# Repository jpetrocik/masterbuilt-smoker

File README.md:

# Smart Smoker Controller System

This project replaces the standard control board in an electric smoker, adding Wi-Fi, PID heat control, four built-in meat probes, a companion mobile app, and more. I can remotely monitor and control the cook from anywhere without being tied down to the smoker. The custom PID algorithm maintains an almost perfect internal temperature with minimal fluctuations. A variety of push notifications eliminate the need to constantly check on the cook throughout the day and night.

The primary goal of this project is to give me my weekend back. I don't want to constantly babysit the smoker when I rather be spending the day snowboarding, hitting trails, off-roading, or just hanging out with friends. The controller continuously monitors the smoker and meat temperature, sending real-time notifications to my phone when probes hit their target temperatures.

This specific board was designed as a drop-in replacement for Masterbuilt refrigerator-style smokers, but the system can be adapted to work with almost any electric smoker.

## Overview

This repository is split into four major components, each with its own detailed `README.md` file:

### 1. Mobile App (./www/README.md)
A Progressive Web App (PWA) that can be installed on your phone to run exactly like a native app, complete with real-time push notifications.

### 2. Backend (./server/README.md)
The central nervous system of the project. It acts as the bridge between the physical smoker and the mobile application. The backend handles the complex algorithms for stall detection and logs high-resolution temperature history. The system is highly fault-tolerant: if the backend drops offline, the firmware will continue executing the active cook locally. If the backend loses connection to the smoker, an alert is sent immediately to your phone.

### 3. Firmware (./firmware/README.md)
The embedded code running on the physical microcontroller (ESP32) that directly interfaces with the smoker's hardware.

### 4. Hardware & PCBs (./hardware/README.md)
This directory contains the custom board designs. Currently, there are two boards designed to support Masterbuilt smokers: the main controller PCB and the power module. The custom power module replaces the stock mechanical relay with a Solid State Relay (SSR) to easily tolerate the rapid on/off switching required by the PID heat control.

## 📂 Repository Structure

```text
├── /server             # Node.js backend
├── /firmware           # Microcontroller code (ESP32/Arduino)
├── /www                # React / Vite / Tailwind PWA
├── /hardware           # Schematics and Gerber files
└── README.md           # Project overview (You are here)

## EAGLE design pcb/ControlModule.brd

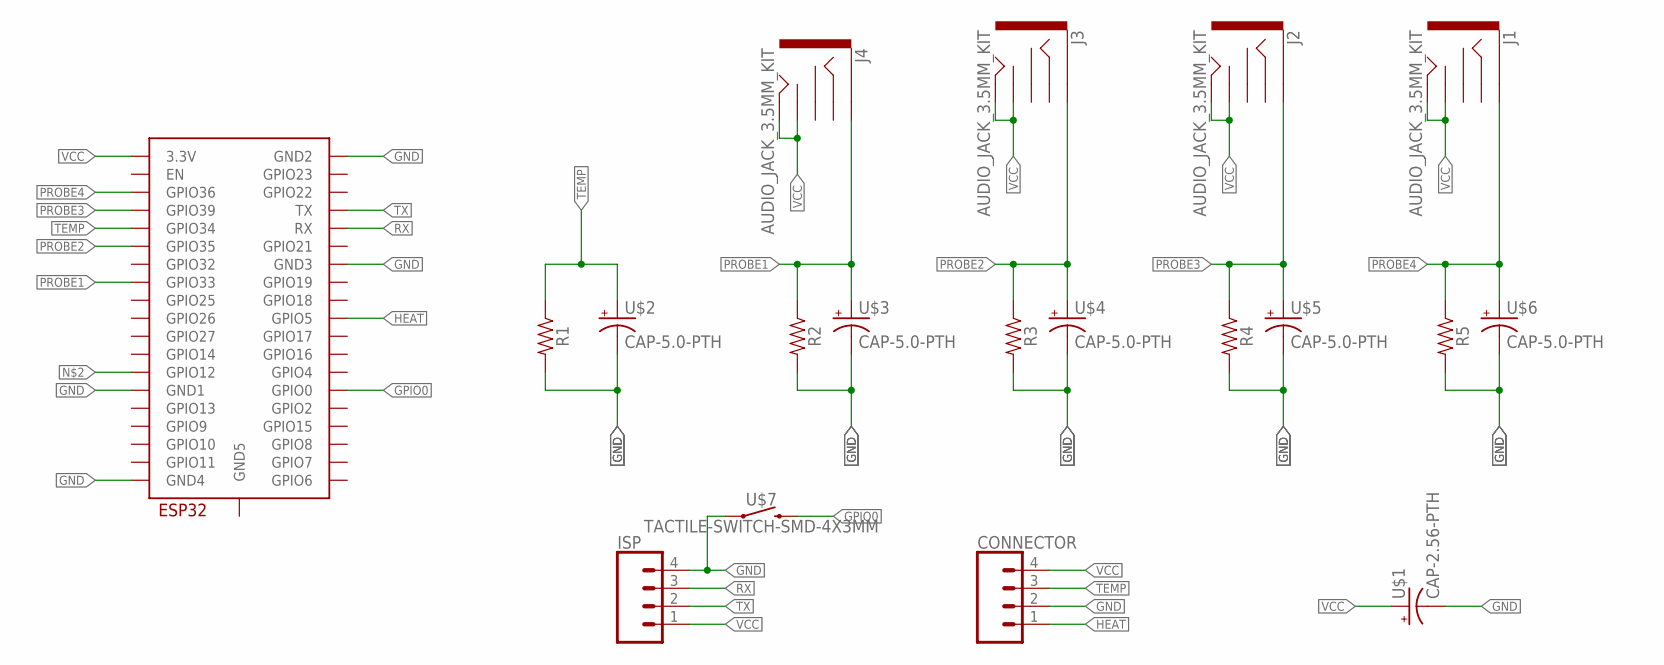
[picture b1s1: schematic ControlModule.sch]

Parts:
CONNECTOR: CONN_04PTH; 1X04
ISP: CONN_04PTH; 1X04
J1, J2, J3, J4: AUDIO_JACK_3.5MM_KIT; AUDIO-JACK-KIT
R1, R2, R3, R4, R5: 0805
U$1: CAP-2.56-PTH; CAP-PTH-2.5MM-5MM
U$2, U$3, U$4, U$5, U$6: CAP-5.0-PTH; CAP-PTH-5MM
U$7: TACTILE-SWITCH-SMD-4X3MM; TACTILE_SWITCH_SMD_4X3MM
U$8: ESP32-WROOM

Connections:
GND: CONNECTOR.2, ISP.4, R1.2, R2.2, R3.2, R4.2, R5.2, U$1.2 (-), U$2.2 (-), U$3.2 (-), U$4.2 (-), U$5.2 (-), U$6.2 (-), U$7.1, U$8.GND1, U$8.GND2, U$8.GND3, U$8.GND4
GPIO0: U$7.2, U$8.IO0 (GPIO0)
HEAT: CONNECTOR.1, U$8.IO5 (GPIO5)
PROBE1: J4.SLEEVE, R2.1, U$3.1 (+), U$8.IO33 (GPIO33)
PROBE2: J3.SLEEVE, R3.1, U$4.1 (+), U$8.IO35 (GPIO35)
PROBE3: J2.SLEEVE, R4.1, U$5.1 (+), U$8.SENSOR_VN (GPIO39)
PROBE4: J1.SLEEVE, R5.1, U$6.1 (+), U$8.SENSOR_VP (GPIO36)
RX: ISP.3, U$8.RX
TEMP: CONNECTOR.3, R1.1, U$2.1 (+), U$8.IO34 (GPIO34)
TX: ISP.2, U$8.TX
VCC: CONNECTOR.4, ISP.1, J1.TIP, J1.TSH, J2.TIP, J2.TSH, J3.TIP, J3.TSH, J4.TIP, J4.TSH, U$1.1 (+), U$8.3V3 (3.3V)

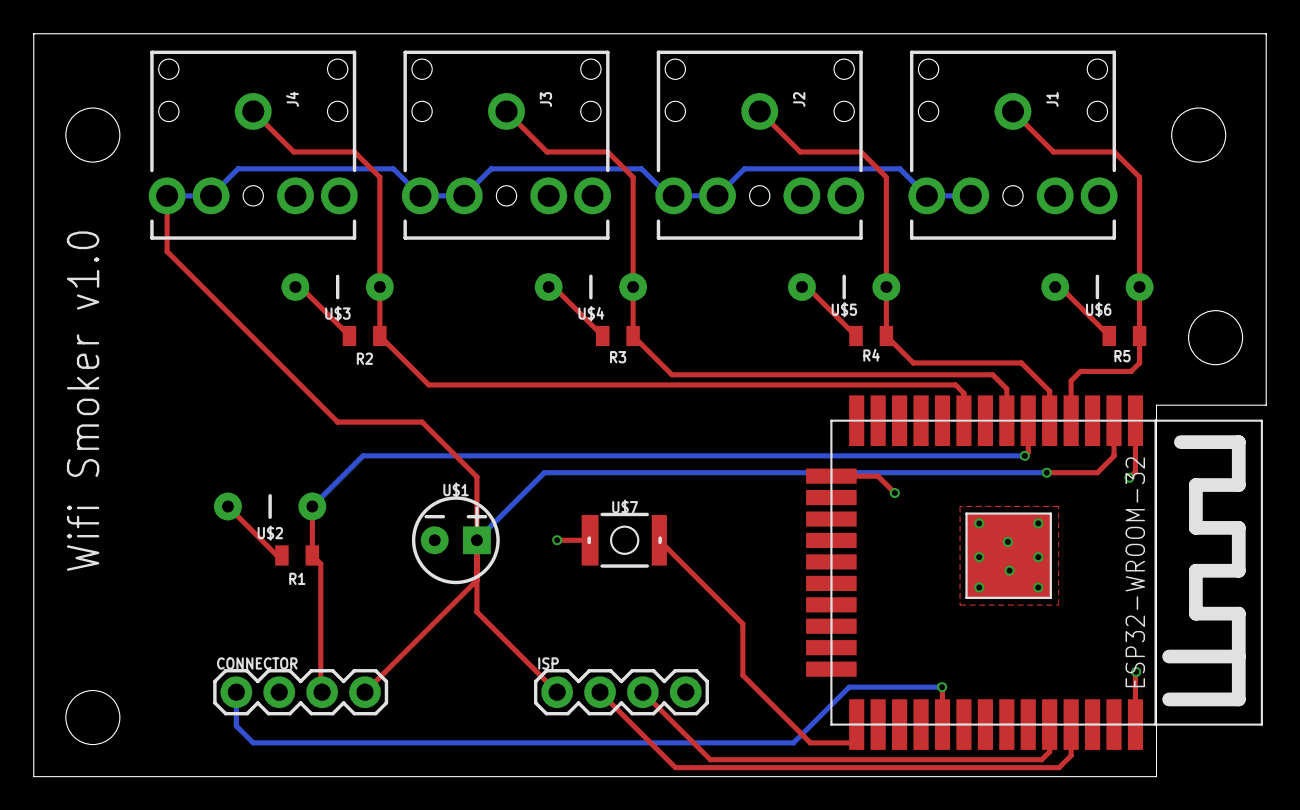
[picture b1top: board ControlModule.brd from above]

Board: 2 copper layers, 73.0 x 44.0 mm, 19 parts (0 on the bottom side), 11 nets.

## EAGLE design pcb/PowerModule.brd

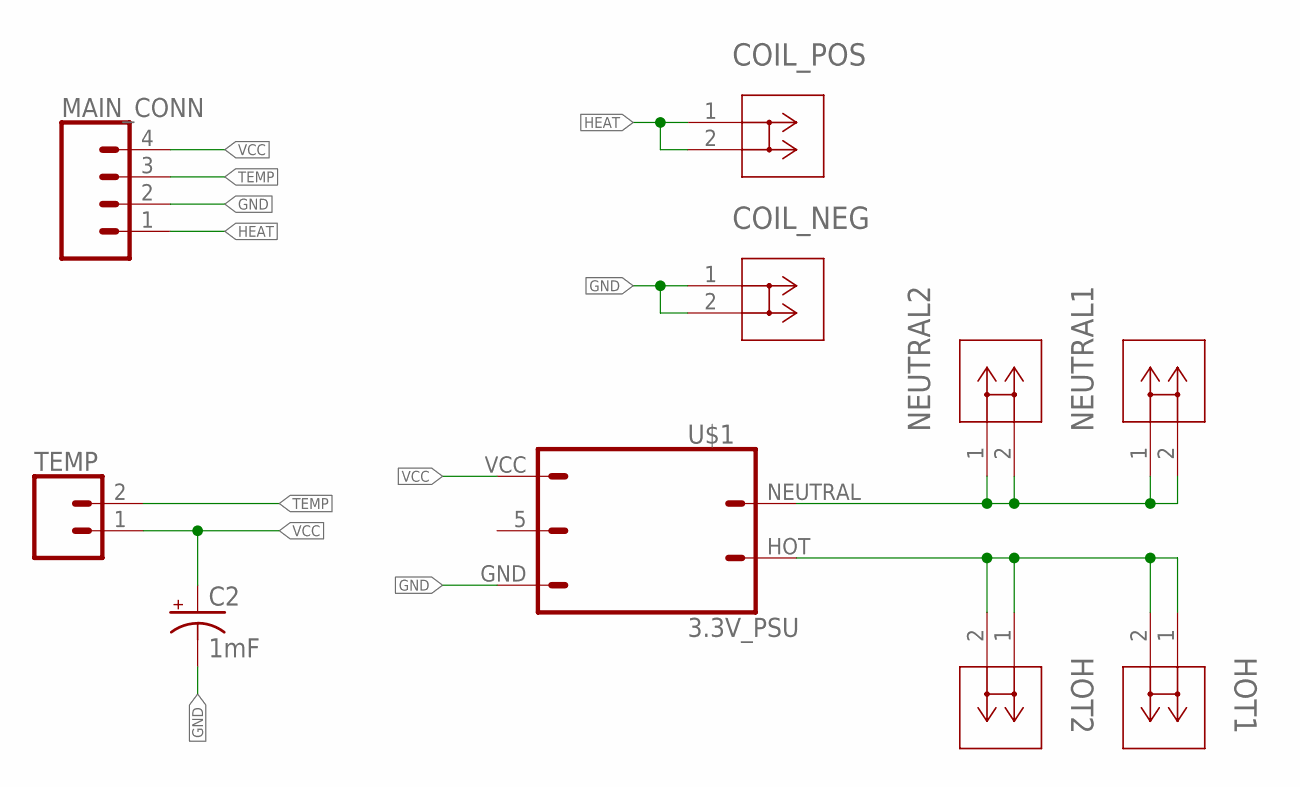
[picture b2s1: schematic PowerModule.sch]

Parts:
C2: 1mF; CPOL-RADIAL-5MM-10MM
COIL_NEG: 1287; CONN_1287_KEY
COIL_POS: 1287; CONN_1287_KEY
HOT1, HOT2: 1287; CONN_1287_KEY
MAIN_CONN: CONN_04PTH; 1X04
NEUTRAL1, NEUTRAL2: 1287; CONN_1287_KEY
TEMP: CONN_02; 1X02
U$1: 3.3V_PSU; 1X03

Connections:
GND: C2.-, COIL_NEG.1, COIL_NEG.2, MAIN_CONN.2, U$1.GND
HEAT: COIL_POS.1, COIL_POS.2, MAIN_CONN.1
HOT: HOT1.1, HOT1.2, HOT2.1, HOT2.2, U$1.HOT
NEUTRAL: NEUTRAL1.1, NEUTRAL1.2, NEUTRAL2.1, NEUTRAL2.2, U$1.NEUTRAL
TEMP: MAIN_CONN.3, TEMP.2
VCC: C2.+, MAIN_CONN.4, TEMP.1, U$1.VCC

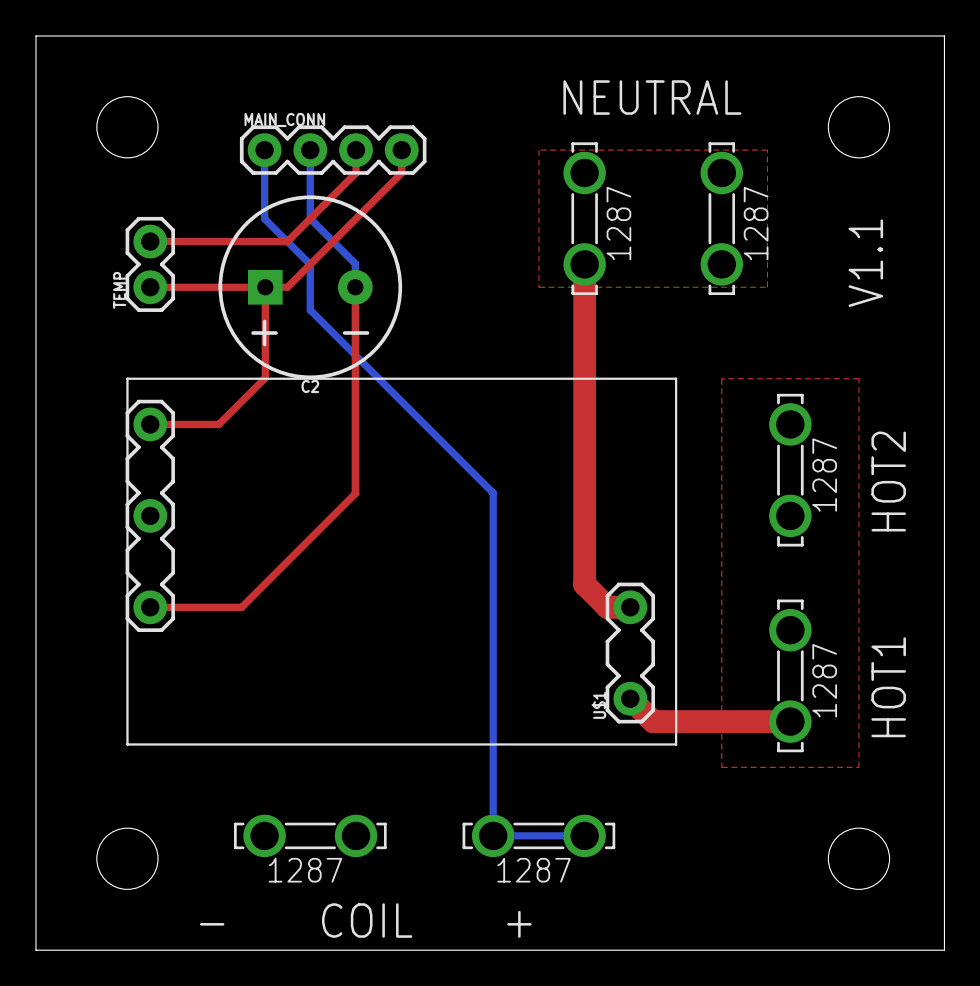
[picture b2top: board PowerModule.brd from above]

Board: 2 copper layers, 50.5 x 50.8 mm, 10 parts (0 on the bottom side), 6 nets.

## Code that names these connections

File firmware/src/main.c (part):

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#define MEAT_PROBE3                  ADC_CHANNEL_3
#define MEAT_PROBE4                  ADC_CHANNEL_4

#define HEAT_PIN 5

#define ADC_SAMPLE_SIZE 8

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cJSON *json = cJSON_Parse("{\"title\":\"Hello World\"}");

    double temperature = 0;
    double probe1 = 0;
    double probe2 = 0;
    double probe3 = 0;
    double probe4 = 0;
    long lastRead = 0;
    long now;
    bool abortError = false;
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
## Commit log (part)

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2022-12-12 Inital commit
2022-12-12 WebSocket
2022-12-12 probes
2022-12-13 No working PID
2022-12-14 Working PID
2022-12-17 Added cookEndTime
2023-01-18 Added probe
2023-02-26 New PROBE_A/B/C
2023-02-27 Added OTA
2023-02-27 Tweaker kp,ki,kd
2023-03-09 Tweaking temp coiffients
2023-03-09 Added eagle files
2023-03-09 Create README.md
    Added readme.md
2023-03-12 using adc functions and new thermistor a/b/c
2023-08-22 Initial commit after some calibration
2023-08-24 Port of PIP
2025-03-12 Add kicad files
2025-05-29 kicad files
2025-05-29 compiles
2025-06-02 Switching to ADS1115
2025-06-03 Probes working with ADS1115
2025-08-02 board version 2.0
2025-08-02 Renamed files
2025-08-12 Removed escape character
2025-08-12 Added developement notes
2025-08-12 Added deep orange theme samples
2025-08-13 Removed bad files
2025-08-13 Added LCD support
2025-08-13 Added define to enable/disable LCD
2025-08-13 upstream lv.conf
2025-08-13 Configure lv.conf file
2025-08-15 Added initial mqqtt support (WIP)
2025-08-15 Configure TFT User_Setup.h
2025-08-15 Moved websoceket and wfi code into sperate files
2025-08-15 Cleaned up UI and better wifi init
2025-08-15 mqtt publish status working
2025-08-15 Changed CommandEvent handling to parse in main.cpp
2025-08-25 Fixed devide by zero error
2025-08-25 Fix overflow issue
2025-08-25 Updated probe ABC numbers
2025-08-26 Temp ABC
2025-08-26 New ABC
2025-08-26 add set check limits
2025-08-26 Cleaned up logging
2025-08-26 Added last will MQTT message
2025-08-27 Added debugProbe and new ABC values
2025-08-27 Added back dutyCycle
2025-08-27 new temp abc
2025-08-27 Cleanup debug code
2025-09-08 Improved PID and ABC settings
2025-09-08 Minor layout improvements
2025-10-06 v2.1 controller
2025-10-06 Added power modules board
2025-10-07 Adding assests
2025-10-07 update board with lcd
2025-10-11 Fixed issue with UI not compiling
2025-10-13 Removed delay in lcd_loop
2026-01-19 Controller v2.1.1
2026-03-11 Added server backend code
2026-03-11 Added missing spec
2026-03-11 SPEC 0.1 complete
2026-03-11 Initial SPEC 0.2
2026-03-11 initial frontend pass
2026-03-11 Updated state information
2026-03-11 Added Elaspe Time
2026-03-12 Added presence LWT and removed device topic code
2026-03-12 Added simulator
2026-03-12 Renames json properties from probe[X][Property] and prefixed smoker
2026-03-12 Fixed boolean issue with sqllite
2026-03-12 Add similutor launch and .gitignore for sqllite data files
2026-03-12 First pass connected to backend
2026-03-12 Fixed infinite loop and localstorage usage
2026-03-12 Fixed display issue with historical data
2026-03-13 Fixed histroical data
2026-03-14 Firebase
2026-03-18 Firebase notification
2026-03-19 SetTemperature
2026-03-19 SetCookTimer
2026-03-19 sendCommand
2026-03-19 WebSocket nanny
2026-03-19 SmokerId picker
2026-03-19 Deployable build
2026-03-19 Make live data renderig faster
2026-03-19 Presences
2026-03-19 functional complete
2026-03-21 Added simulator command line arguments
2026-03-21 Fixed issue with parsing command line arguments
2026-03-21 Fixed mixed up between probeTemp and probeTarget
2026-03-21 Added manifest
2026-03-23 Create icon assests and icons
2026-03-24 Improved temperature simulation
2026-03-24 Added stale notification and cleaned up notification code
2026-03-24 Improve the telemetry data requirement based on calculated telemetry intervals
2026-03-24 Speed up probe telemetry growth
2026-03-24 Fixed issue with alert on new smoker
2026-03-24 Default notification to true so on startup they are not fired
2026-03-24 Fixed elasped time display to round down
2026-03-24 Fixed issue with timer alter not sending if the timer is reset after the sending and alert the first time
2026-03-25 Fixed issue with history getting deleted on restart
2026-03-25 Rename run script names
2026-03-25 Fixed issue with graph not showing historical data when ws reconnects
2026-03-25 Changed smoker list from last seen to status
2026-03-26 Added time delay notifcation for offline smoker
2026-03-26 Removed offline purge logic
2026-03-26 Reduce historical data to 1 record per minute
2026-03-26 Fix historical record count log message
2026-03-26 Added clickable carousel dot for desktop useablity
2026-03-31 Gated temp between 0 and 300
2026-03-31 Reload smokers when manually launching smoker picker
2026-05-22 Fixed truncated status messages
2026-05-22 Fixed issue with temp increament and decreament button on trigger correctly

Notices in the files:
parts and their libraries:
SparkFun-Connectors: Licensing: Creative Commons ShareAlike 4.0 International - https://creativecommons.org/licenses/by-sa/4.0
COPYRIGHT: Copyright (C) 2022 Ultra Librarian. All rights reserved.
